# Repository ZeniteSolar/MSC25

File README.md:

# Módulo Sensor de Corrente(MSC25)

## Visão Geral

Este projeto consiste em uma placa de circuito impresso (PCB) com firmware embarcado, projetada para realizar a leitura de alta precisão de um sensor de corrente de efeito Hall e transmitir os dados através do barramento CAN.

O firmware foi desenvolvido em C para microcontroladores AVR, seguindo uma arquitetura modular, não-bloqueante e orientada por eventos, garantindo robustez e tempo de resposta previsível. O sistema é configurado e compilado utilizando um ambiente `avr-gcc` e `make`.

## Principais Características

* **Microcontrolador:** ATmega328P operando a 16MHz.
* **Comunicação:** Interface CAN Bus 2.0A (11-bit) implementada com controlador dedicado MCP2515 e transceptor MCP2561.
* **Leitura de Sensor:** Interface analógica de alta precisão para sensores de corrente, com condicionamento de sinal.
* **Fonte de Alimentação:** Sistema de alimentação robusto com fonte simétrica isolada para o estágio analógico.
* **Modos de Leitura:** Firmware com modos de operação configuráveis em tempo de compilação:
    * **Modo Média Móvel:** Fornece leituras estáveis, ideal para monitoramento de estado.
    * **Modo Instantâneo:** Fornece a última leitura bruta, ideal para captura de picos e transientes de corrente.
* **Arquitetura de Firmware:** Modular, baseada em máquina de estados e interrupções de hardware para tarefas periódicas.

## Detalhes do Hardware

O hardware foi projetado para garantir a integridade do sinal e a robustez da comunicação.

### Fonte de Alimentação

A placa recebe uma tensão de entrada de 18V, que é regulada internamente para os domínios digitais e analógicos:

* **+12V:** Gerado por um regulador LM7812 para alimentar periféricos e o estágio de amplificação.
* **+5V:** Gerado por um regulador LM7805 para alimentar o microcontrolador ATmega328P e o controlador CAN MCP2515.

#### Fonte Simétrica Isolada (±15V)

Para a correta polarização do sensor de corrente e do circuito de condicionamento analógico, foi implementada uma fonte simétrica de ±15V. Esta etapa utiliza dois conversores DC/DC isolados do tipo **PDSE1-S5-S15-S**. A partir da entrada de +5V, cada conversor gera uma tensão de saída isolada (+15V e -15V, respectivamente). A isolação galvânica garante que ruídos do barramento de alimentação principal não interfiram na precisão das medições analógicas.

### Sensor e Condicionamento de Sinal

O circuito foi projetado para interfacear com um sensor de corrente de efeito Hall, como o **SECOHR 200SCV**.

O sinal de saída do sensor é processado por um circuito de condicionamento baseado no amplificador operacional **LM324**. Este estágio tem a função de amplificar e deslocar o nível de tensão (offset) do sinal, ajustando-o para a faixa de leitura do conversor Analógico-Digital (ADC) do ATmega328P (0-5V). O resultado é um sinal robusto e centralizado, que permite a medição de correntes tanto positivas quanto negativas.

## Detalhes do Firmware

O firmware é escrito em C puro (padrão gnu99) e compilado com `avr-gcc`.

### Arquitetura

A lógica principal é controlada por uma máquina de estados (`machine.c`) que é executada em uma frequência fixa de 100 Hz, controlada pela interrupção do `Timer2`. A leitura do ADC é desacoplada da lógica principal, sendo disparada pelo `Timer0` a uma frequência de 1000 Hz e processada através de interrupções (`ISR(ADC_vect)`), garantindo que as amostragens ocorram de forma consistente. A comunicação entre a rotina de interrupção e o laço principal é feita através de flags voláteis para evitar condições de corrida.

### Módulos Principais

* **`main`**: Ponto de entrada, inicialização dos periféricos e laço principal.
* **`adc`**: Gerencia a configuração do ADC, o disparo por timer, a rotina de interrupção e as funções de processamento (média e leitura instantânea). Inclui um placeholder para **linearização** do sensor.
* **`machine`**: Contém a máquina de estados principal e a lógica de aplicação.
* **`can_app`**: Camada de aplicação do protocolo CAN. Responsável por montar e enviar as mensagens nos intervalos corretos.
* **`conf`**: Arquivo de cabeçalho central para todas as configurações de compilação, como ativação de módulos e seleção de modos de operação.

## Protocolo CAN

A placa se identifica na rede CAN e transmite duas mensagens principais.

* **Nome do Módulo:** `MSC25_1`
* **Assinatura (Signature):** `195` (0xC3)

| Mensagem | ID (Hex) | ID (Dec) | Frequência | Tamanho | Payload |
| :--- | :---: | :---: | :---: | :---: | :--- |
| **State** | `0x79` | 121 | 1 Hz | 3 Bytes | `[Assinatura, Estado, Erro]` |
| **Measurements** | `0xF0` | 240 | 10 Hz | 3 Bytes | `[Assinatura, Corrente_L, Corrente_H]` |

## Ambiente de Desenvolvimento

* **Toolchain:** `avr-gcc`, `avr-libc`, `make`
* **Programador:** `avrdude` (configurado para `arduino`)
* **Biblioteca Principal:** `avr-can-lib` (deve estar presente na pasta `lib/`)

## Como Compilar e Gravar

1.  **Preparar Bibliotecas:** Execute o script para compilar a `avr-can-lib` e baixar o `can_ids.h` mais recente.
    ```bash
    ./makelibs.sh
    ```

2.  **Compilar o Projeto:** Use o comando `make` para compilar todo o código-fonte.
    ```bash
    make
    ```

3.  **Limpar o Projeto:** Para apagar os arquivos compilados.
    ```bash
    make clean
    ```

4.  **Gravar na Placa:** Para compilar (se necessário) e gravar o firmware no microcontrolador.
    ```bash
    make flash
    ```
5.  **Fazer Tudo (Limpar, Compilar, Gravar e Monitorar):**
    ```bash
    ./up.sh
    ```

 ## Precisa adicionar ao can_ids.h
  ```
 // MSC25_1 - Módulo Sensor de Corrente (Sua Nova Placa)
#define CAN_SIGNATURE_MSC25_1 195
// MSC25_1 - STATE - Module state report
#define CAN_MSG_MSC25_1_STATE_ID 121
#define CAN_MSG_MSC25_1_STATE_LENGTH 3
#define CAN_MSG_MSC25_1_STATE_FREQUENCY 1
#define CAN_MSG_MSC25_1_STATE_SIGNATURE_BYTE 0 //<!" Senders signature
#define CAN_MSG_MSC25_1_STATE_STATE_BYTE 1     //<!" State code
#define CAN_MSG_MSC25_1_STATE_ERROR_BYTE 2     //<!" Error code

// MSC25_1 - MEASUREMENTS - Current measurements from the sensor
#define CAN_MSG_MSC25_1_MEASUREMENTS_ID 240
#define CAN_MSG_MSC25_1_MEASUREMENTS_LENGTH 3
#define CAN_MSG_MSC25_1_MEASUREMENTS_FREQUENCY 10
#define CAN_MSG_MSC25_1_MEASUREMENTS_SIGNATURE_BYTE 0    //<!" Senders signature
#define CAN_MSG_MSC25_1_MEASUREMENTS_CURRENT_L_BYTE 1    //<!" Average current, byte low
#define CAN_MSG_MSC25_1_MEASUREMENTS_CURRENT_H_BYTE 2    //<!" Average current, byte high
```

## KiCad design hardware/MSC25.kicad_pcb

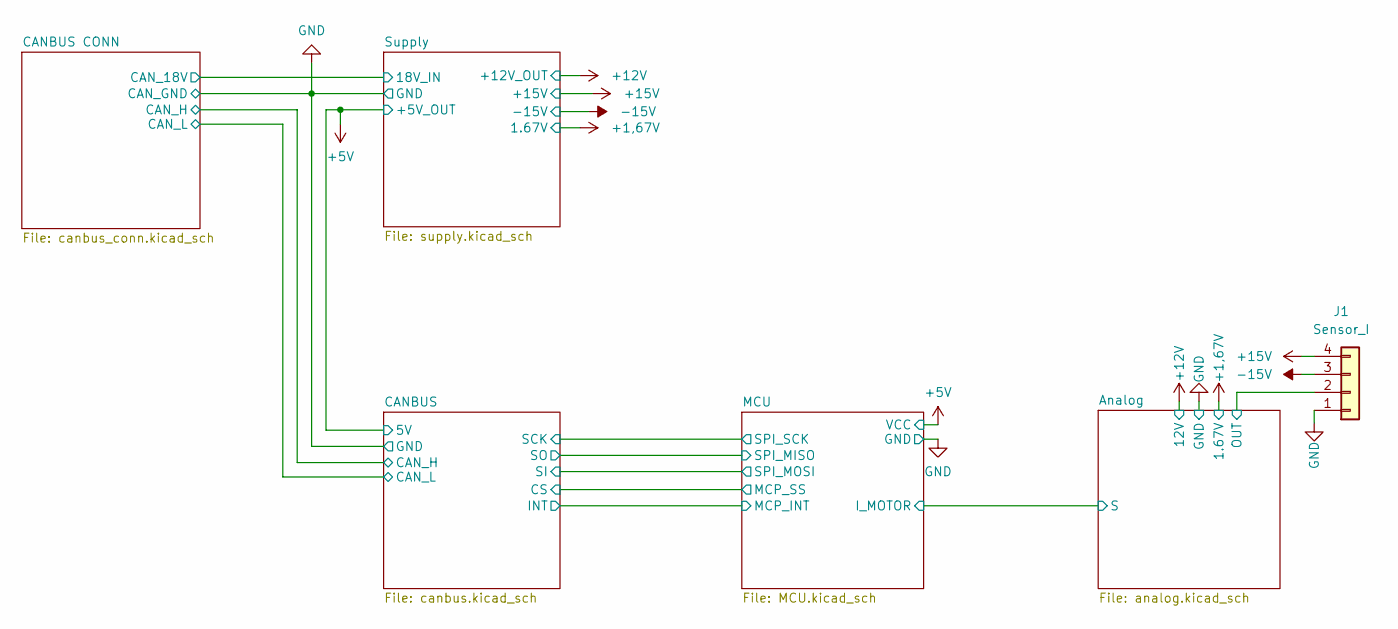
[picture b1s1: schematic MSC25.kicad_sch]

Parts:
J1: Sensor_I; PinHeader_1x04_P2.54mm_Vertical

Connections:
+15V: J1.4; also elsewhere on the board
-15V: J1.3; also elsewhere on the board
/Analog/OUT: J1.2; also elsewhere on the board
GND: J1.1; also elsewhere on the board

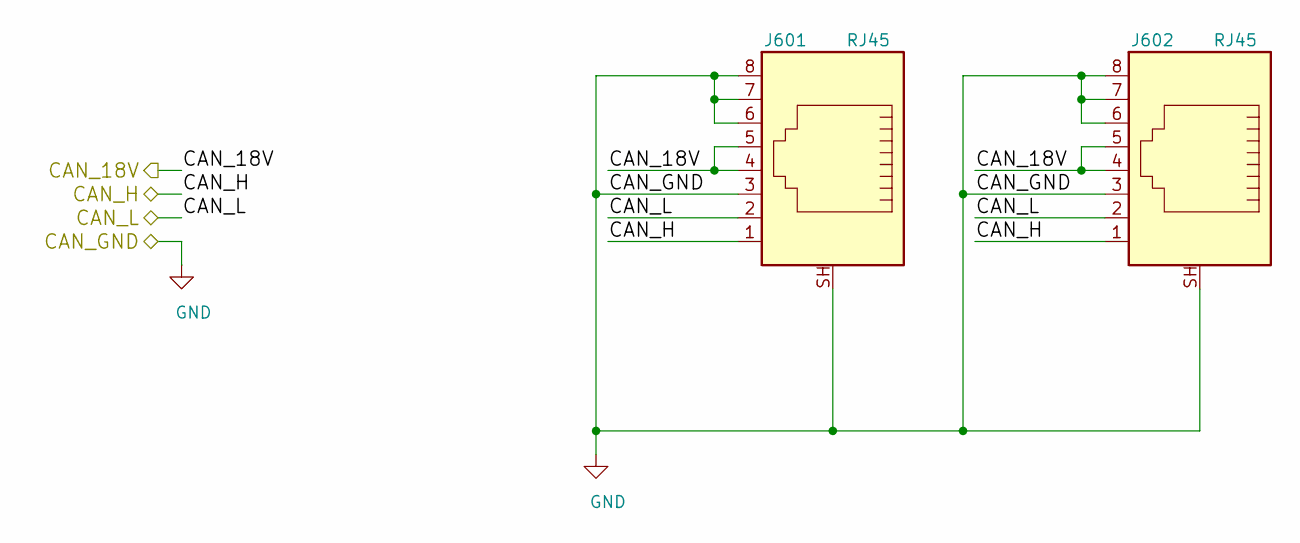
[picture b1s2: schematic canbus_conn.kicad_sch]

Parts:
J601, J602: RJ45; RJ45_YH59_01

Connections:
/CANBUS CONN/CAN_18V: J601.4, J601.5, J602.4, J602.5; also elsewhere on the board
/CANBUS CONN/CAN_H: J601.1, J602.1; also elsewhere on the board
/CANBUS CONN/CAN_L: J601.2, J602.2; also elsewhere on the board
GND: J601.3, J601.6, J601.7, J601.8, J601.SH, J602.3, J602.6, J602.7, J602.8, J602.SH; also elsewhere on the board

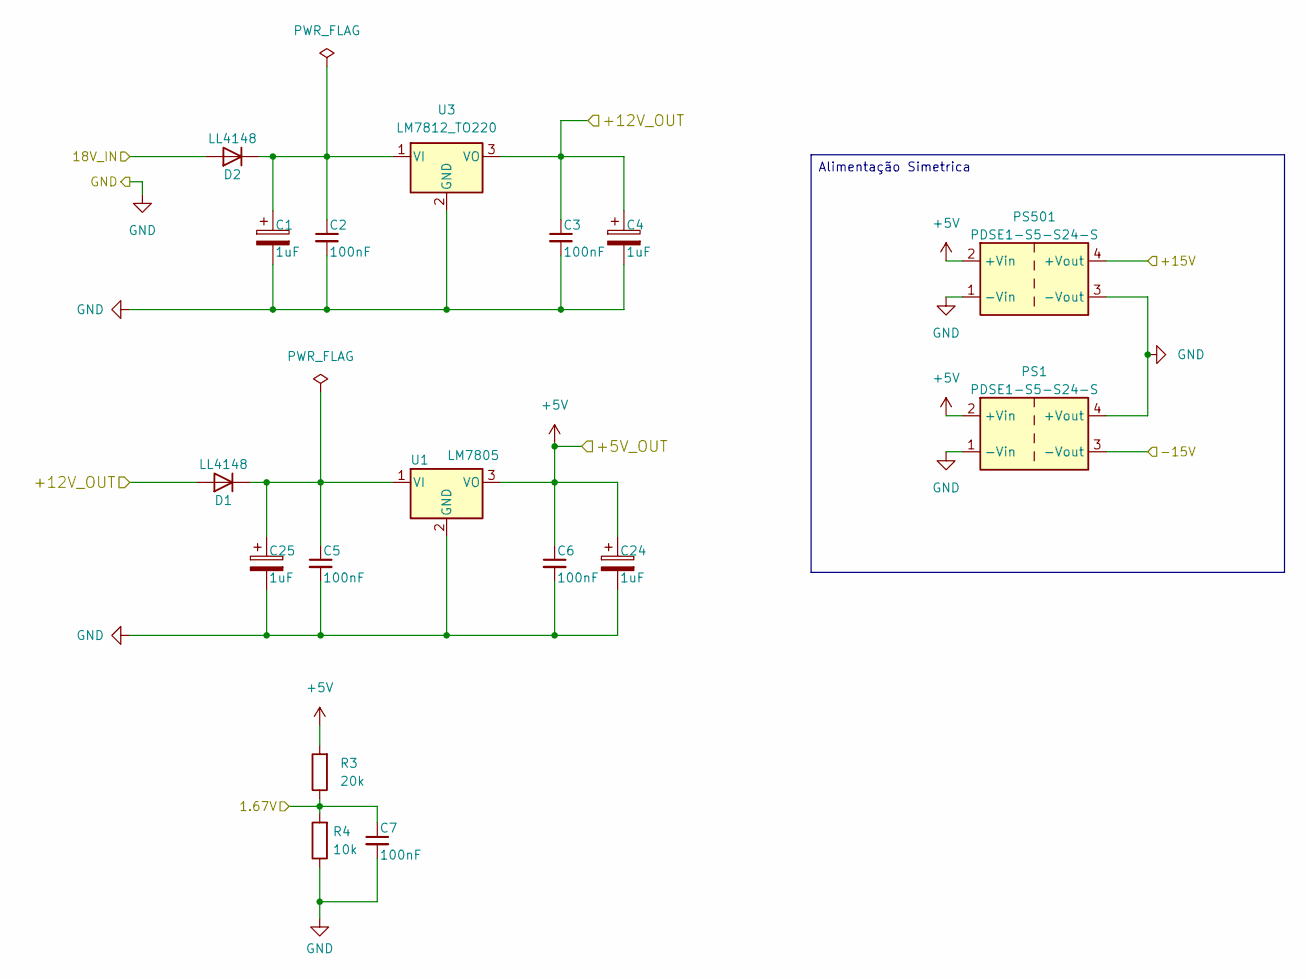
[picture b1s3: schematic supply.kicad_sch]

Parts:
C1, C4, C24, C25: 1uF; CP_EIA-6032-15_Kemet-U_HandSolder
C2, C3, C5, C6, C7: 100nF; C_0805_2012Metric_Pad1.18x1.45mm_HandSolder
D1, D2: LL4148; D_MiniMELF_Handsoldering
PS1, PS501: PDSE1-S5-S24-S; Converter_DCDC_Murata_MEE3SxxxxSC_THT
R3: 20k; R_0805_2012Metric_Pad1.20x1.40mm_HandSolder
R4: 10k; R_0805_2012Metric_Pad1.20x1.40mm_HandSolder
U1: LM7805; TO-220-3_Horizontal_TabDown
U3: LM7812_TO220; TO-220-3_Horizontal_TabDown

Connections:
+1,67V: C7.1, R3.1, R4.2; also elsewhere on the board
+5V: C6.1, C24.1, PS1.2 (+Vin), PS501.2 (+Vin), R3.2, U1.3 (VO); also elsewhere on the board
+12V: C3.1, C4.1, D1.2 (A), U3.3 (VO); also elsewhere on the board
+15V: PS501.4 (+Vout); also elsewhere on the board
-15V: PS1.3 (-Vout); also elsewhere on the board
/CANBUS CONN/CAN_18V: D2.2 (A); also elsewhere on the board
GND: C1.2, C2.2, C3.2, C4.2, C5.2, C6.2, C7.2, C24.2, C25.2, PS1.1 (-Vin), PS1.4 (+Vout), PS501.1 (-Vin), PS501.3 (-Vout), R4.1, U1.2 (GND), U3.2 (GND); also elsewhere on the board
unnamed: C5.1, C25.1, D1.1 (K), U1.1 (VI)
unnamed: C1.1, C2.1, D2.1 (K), U3.1 (VI)

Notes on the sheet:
Alimentação Simetrica

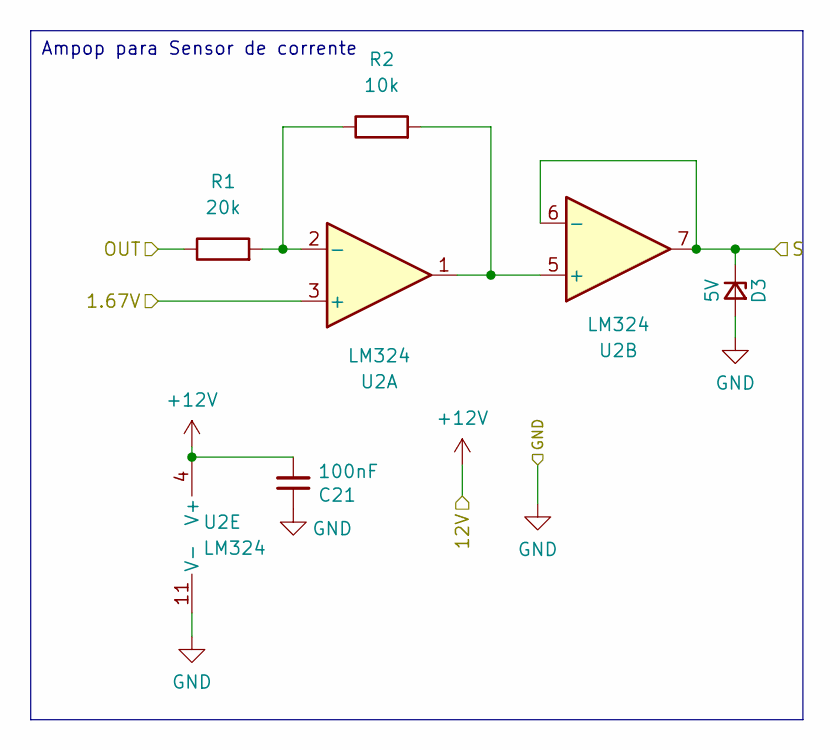
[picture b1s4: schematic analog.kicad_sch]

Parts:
C21: 100nF; C_0805_2012Metric_Pad1.18x1.45mm_HandSolder
D3: 5V; D_MiniMELF
R1: 20k; R_0805_2012Metric_Pad1.20x1.40mm_HandSolder
R2: 10k; R_0805_2012Metric_Pad1.20x1.40mm_HandSolder
U2: LM324

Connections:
+1,67V: U2.3 (+); also elsewhere on the board
+12V: C21.2, U2.4 (V+); also elsewhere on the board
/Analog/OUT: R1.1; also elsewhere on the board
/Analog/S: D3.1 (K), U2.6 (-), U2.7; also elsewhere on the board
GND: C21.1, D3.2 (A), U2.11 (V-); also elsewhere on the board
unnamed: R1.2, R2.1, U2.2 (-)
unnamed: R2.2, U2.1, U2.5 (+)

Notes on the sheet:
Ampop para Sensor de corrente

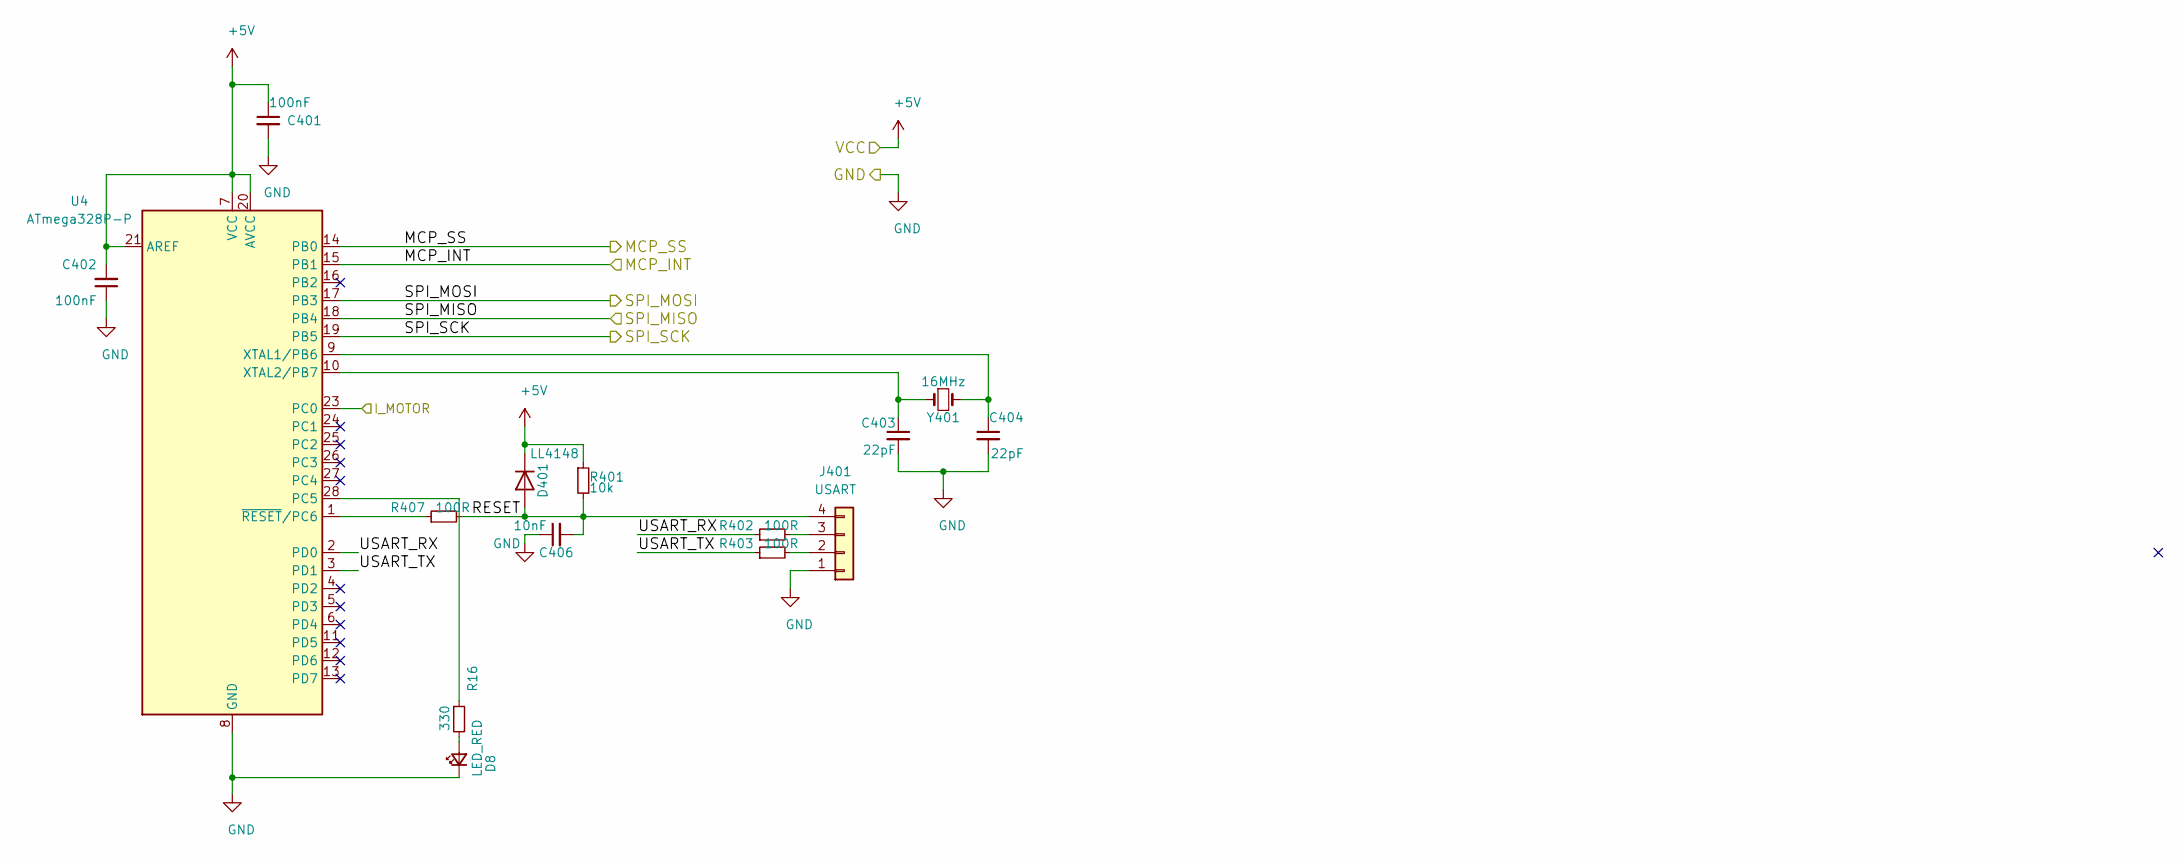
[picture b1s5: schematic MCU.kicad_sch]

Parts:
C401, C402: 100nF; C_0805_2012Metric_Pad1.18x1.45mm_HandSolder
C403, C404: 22pF; C_0805_2012Metric_Pad1.18x1.45mm_HandSolder
C406: 10nF; C_0805_2012Metric_Pad1.18x1.45mm_HandSolder
D8: LED_RED; LED_0805_2012Metric_Pad1.15x1.40mm_HandSolder
D401: LL4148; D_MiniMELF_Handsoldering
J401: USART; PinHeader_1x04_P2.54mm_Vertical
R16: 330; R_0805_2012Metric_Pad1.20x1.40mm_HandSolder
R401: 10k; R_0805_2012Metric_Pad1.20x1.40mm_HandSolder
R402, R403, R407: 100R; R_0805_2012Metric_Pad1.20x1.40mm_HandSolder
U4: ATmega328P-P; DIP-28_W7.62mm_LongPads
Y401: 16MHz; Crystal_HC49-U_Vertical

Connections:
+5V: C401.1, C402.2, D401.1 (K), R401.1, U4.7 (VCC), U4.20 (AVCC), U4.21 (AREF); also elsewhere on the board
/Analog/S: U4.23 (PC0); also elsewhere on the board
/MCU/MCP_INT: U4.15 (PB1); also elsewhere on the board
/MCU/MCP_SS: U4.14 (PB0); also elsewhere on the board
/MCU/RESET: C406.2, D401.2 (A), J401.4, R401.2, R407.2
/MCU/SPI_MISO: U4.18 (PB4); also elsewhere on the board
/MCU/SPI_MOSI: U4.17 (PB3); also elsewhere on the board
/MCU/SPI_SCK: U4.19 (PB5); also elsewhere on the board
/MCU/USART_RX: R402.1, U4.2 (PD0)
/MCU/USART_TX: R403.1, U4.3 (PD1)
GND: C401.2, C402.1, C403.2, C404.2, C406.1, D8.1 (K), J401.1, U4.8 (GND), U4.22 (GND); also elsewhere on the board
unnamed: D8.2 (A), R16.2
unnamed: J401.2, R403.2
unnamed: J401.3, R402.2
unnamed: R16.1, U4.28 (PC5)
unnamed: C404.1, U4.9 (XTAL1/PB6), Y401.2
unnamed: C403.1, U4.10 (XTAL2/PB7), Y401.1
unnamed: R407.1, U4.1 (~RESET/PC6)

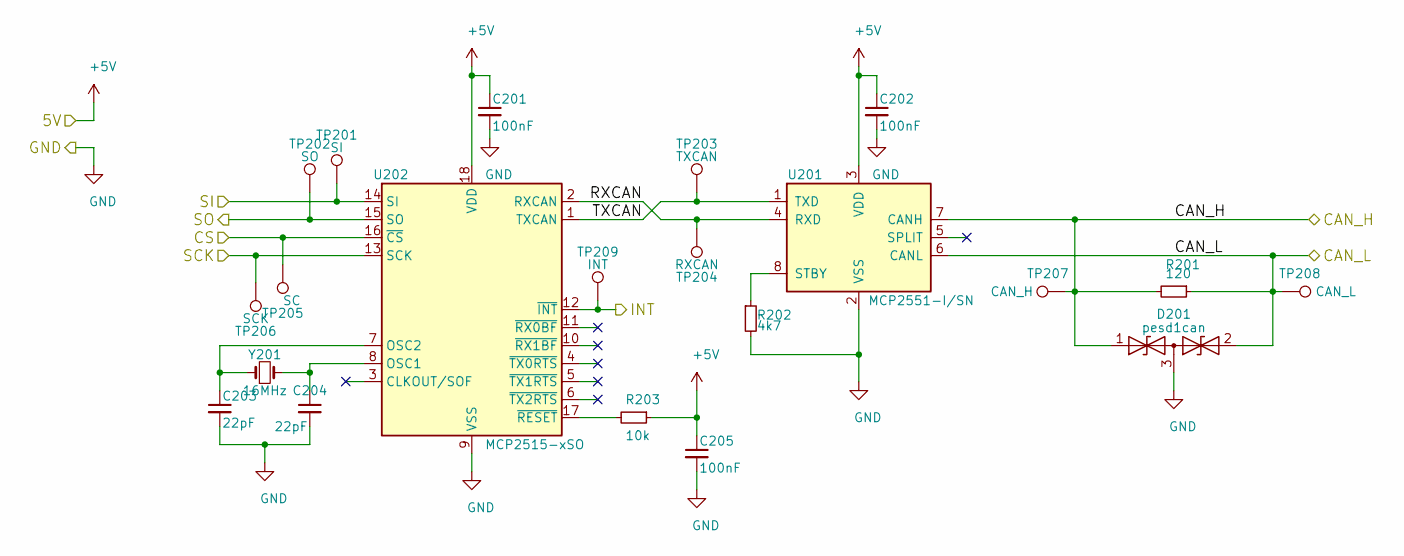
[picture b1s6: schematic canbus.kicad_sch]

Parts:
C201, C202, C205: 100nF; C_0805_2012Metric_Pad1.18x1.45mm_HandSolder
C203, C204: 22pF; C_0805_2012Metric_Pad1.18x1.45mm_HandSolder
D201: pesd1can; SOT-23_Handsoldering
R201: 120; R_0805_2012Metric_Pad1.20x1.40mm_HandSolder
R202: 4k7; R_0805_2012Metric_Pad1.20x1.40mm_HandSolder
R203: 10k; R_0805_2012Metric_Pad1.20x1.40mm_HandSolder
TP201: SI; TestPoint_Pad_D1.5mm
TP202: SO; TestPoint_Pad_D1.5mm
TP203: TXCAN; TestPoint_Pad_D1.5mm
TP204: RXCAN; TestPoint_Pad_D1.5mm
TP205: SC; TestPoint_Pad_D1.5mm
TP206: SCK; TestPoint_Pad_D1.5mm
TP207: CAN_H; TestPoint_Pad_D1.5mm
TP208: CAN_L; TestPoint_Pad_D1.5mm
TP209: INT; TestPoint_Pad_D1.5mm
U201: MCP2551-I/SN; SOIC-8_3.9x4.9mm_P1.27mm
U202: MCP2515-xSO; SOIC-18W_7.5x11.6mm_P1.27mm
Y201: 16MHz; Crystal_HC49-U_Vertical

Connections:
+5V: C201.1, C202.1, C205.1, R203.1, U201.3 (VDD), U202.18 (VDD); also elsewhere on the board
/CANBUS CONN/CAN_H: D201.1 (A1), R201.2, TP207.1, U201.7 (CANH); also elsewhere on the board
/CANBUS CONN/CAN_L: D201.2 (A2), R201.1, TP208.1, U201.6 (CANL); also elsewhere on the board
/CANBUS/RXCAN: TP204.1, U201.4 (RXD), U202.2 (RXCAN)
/CANBUS/TXCAN: TP203.1, U201.1 (TXD), U202.1 (TXCAN)
/MCU/MCP_INT: TP209.1, U202.12 (~INT); also elsewhere on the board
/MCU/MCP_SS: TP205.1, U202.16 (~CS); also elsewhere on the board
/MCU/SPI_MISO: TP202.1, U202.15 (SO); also elsewhere on the board
/MCU/SPI_MOSI: TP201.1, U202.14 (SI); also elsewhere on the board
/MCU/SPI_SCK: TP206.1, U202.13 (SCK); also elsewhere on the board
GND: C201.2, C202.2, C203.2, C204.2, C205.2, D201.3 (common), R202.2, U201.2 (VSS), U202.9 (VSS); also elsewhere on the board
unnamed: R202.1, U201.8 (STBY)
unnamed: C204.1, U202.8 (OSC1), Y201.2
unnamed: C203.1, U202.7 (OSC2), Y201.1
unnamed: R203.2, U202.17 (~RESET)

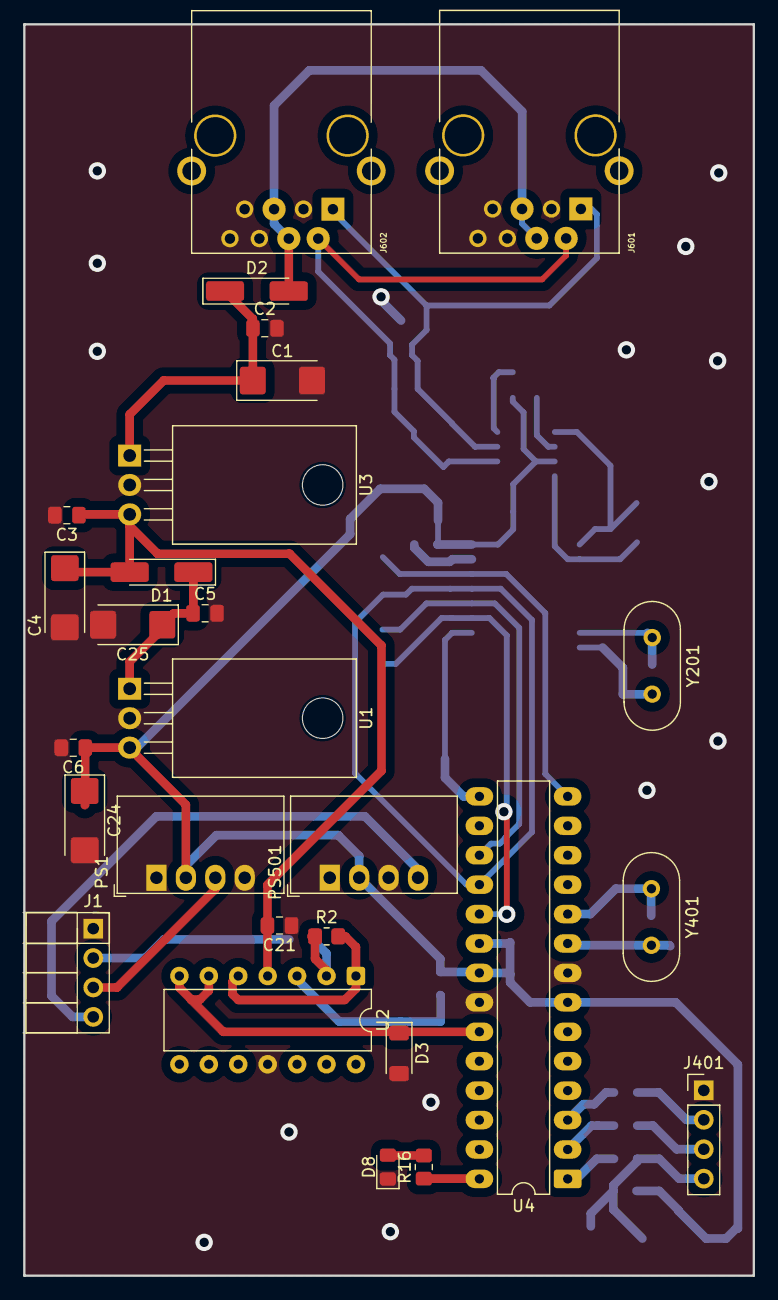
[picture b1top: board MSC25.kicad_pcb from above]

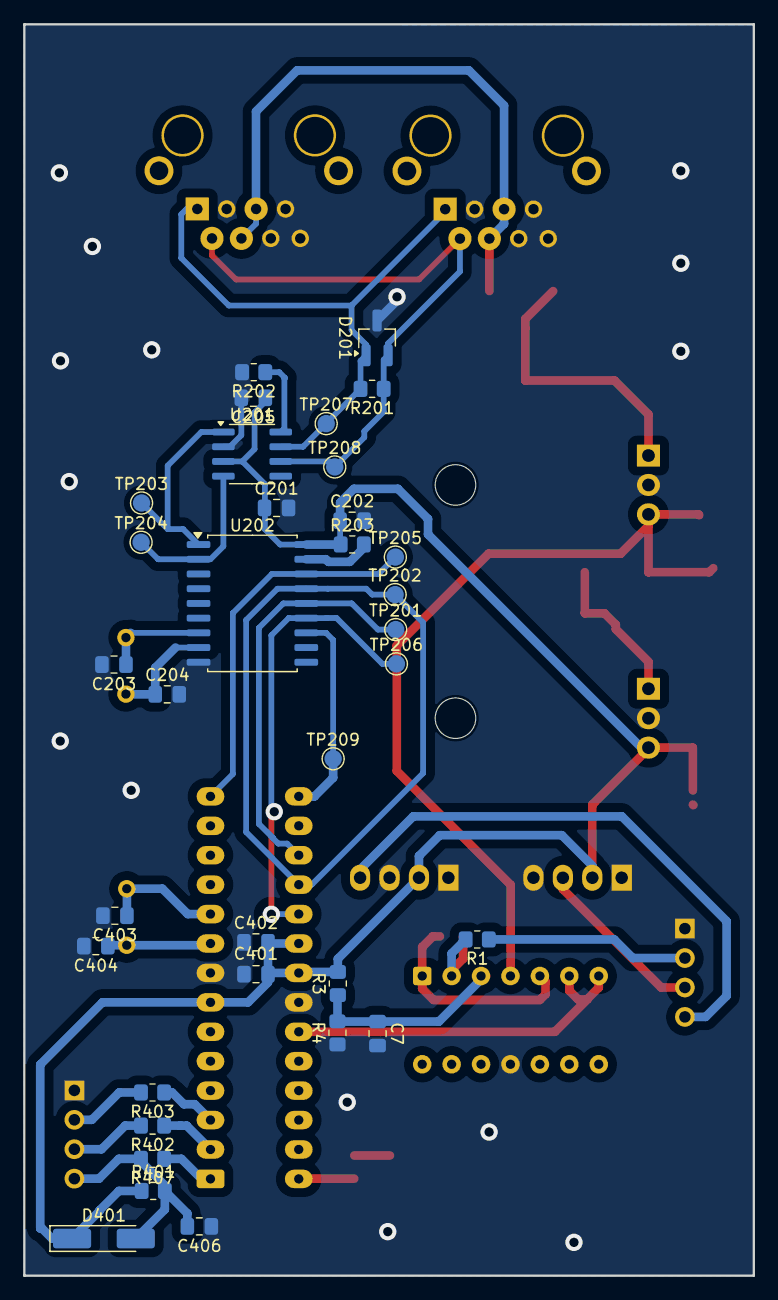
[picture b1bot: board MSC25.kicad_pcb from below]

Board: 2 copper layers, 63.0 x 108.0 mm, 61 parts (34 on the bottom side), 36 nets.

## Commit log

2025-09-19 adicionando arquivos
2025-09-19 Remove arquivos ignorados do repositório
2025-09-19 adicionando arquivos firmware
2025-09-19 atualizando arquivos
2025-09-19 atualização
2025-09-20 Remove Zone.Identifier and kicad backups
2025-09-20 Added -backups to ignore new kicad version backups
2025-09-26 adicionando gerbers e atualização
2025-09-26 atualizações
2026-06-03 adicionando arquivos finais
